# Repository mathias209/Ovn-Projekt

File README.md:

# Repo til vores ovnprojekt
beskrivelse go here

rapporter ligger i onedrive
rapport i word er her:
[Rapport](https://dtudk-my.sharepoint.com/:w:/r/personal/s256053_dtu_dk/Documents/Desktop/Projects/Ovn%20project.docx?d=wf24f0aff373c4a23b3fe023b4cf325e0&csf=1&web=1&e=GDiYzS)

[link til gruppe arbejde i Stens timer](https://github.com/mathias209/Elektroteknik-gruppearbejde)

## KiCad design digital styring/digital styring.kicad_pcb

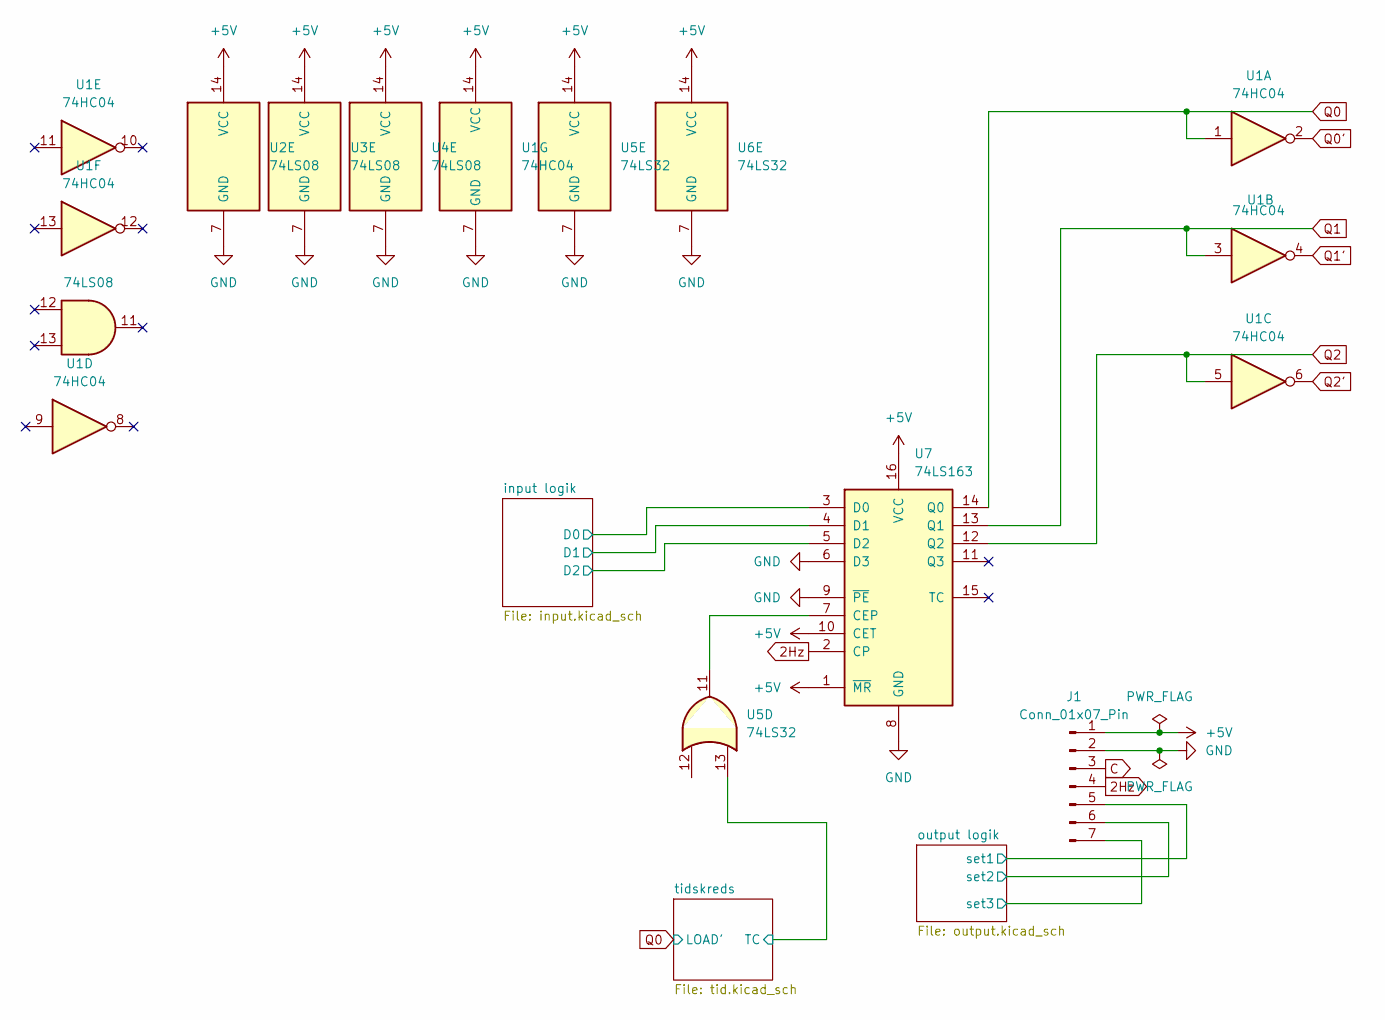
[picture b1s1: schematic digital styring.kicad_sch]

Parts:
J1: Conn_01x07_Pin; PinSocket_1x07_P2.54mm_Vertical
U1: 74HC04; DIP-14_W7.62mm_LongPads
U2, U3, U4: 74LS08; DIP-14_W7.62mm_LongPads
U5, U6: 74LS32; DIP-14_W7.62mm_LongPads
U7: 74LS163; DIP-16_W7.62mm_LongPads

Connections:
2Hz: J1.4, U7.2 (CP); also elsewhere on the board
+5V: J1.1, U1.14 (VCC), U2.14 (VCC), U3.14 (VCC), U4.14 (VCC), U5.14 (VCC), U6.14 (VCC), U7.1 (~MR), U7.10 (CET), U7.16 (VCC); also elsewhere on the board
/input logik/D0: U7.3 (D0); also elsewhere on the board
/input logik/D1: U7.4 (D1); also elsewhere on the board
/input logik/D2: U7.5 (D2); also elsewhere on the board
/output logik/set2: J1.6; also elsewhere on the board
/tidskreds/TC: U5.13; also elsewhere on the board
C: J1.3; also elsewhere on the board
GND: J1.2, U1.7 (GND), U2.7 (GND), U3.7 (GND), U4.7 (GND), U5.7 (GND), U6.7 (GND), U7.6 (D3), U7.8 (GND), U7.9 (~PE); also elsewhere on the board
unnamed: U5.11, U7.7 (CEP)
Q0: U1.1, U7.14 (Q0); also elsewhere on the board
Q0': U1.2, U5.12; also elsewhere on the board
Q1: U1.3, U7.13 (Q1); also elsewhere on the board
Q1': J1.5, U1.4
Q2: J1.7, U1.5, U7.12 (Q2); also elsewhere on the board
Q2': U1.6; also elsewhere on the board

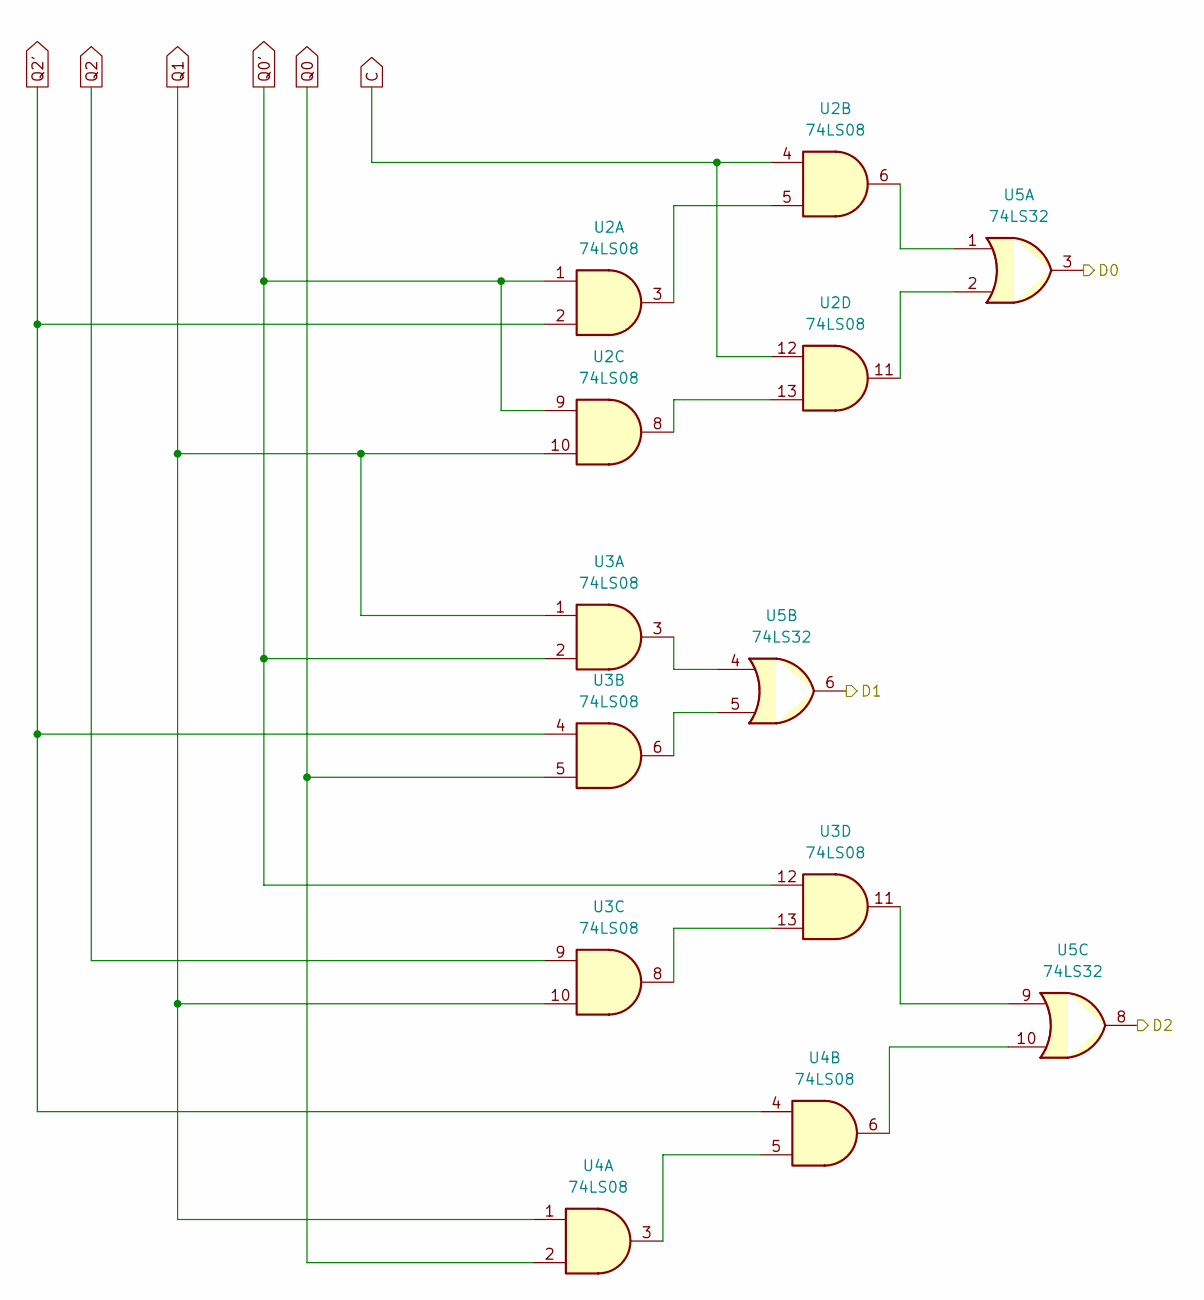
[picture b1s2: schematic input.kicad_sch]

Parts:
U2, U3, U4: 74LS08; DIP-14_W7.62mm_LongPads
U5: 74LS32; DIP-14_W7.62mm_LongPads

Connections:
/input logik/D0: U5.3; also elsewhere on the board
/input logik/D1: U5.6; also elsewhere on the board
/input logik/D2: U5.8; also elsewhere on the board
C: U2.4, U2.12; also elsewhere on the board
unnamed: U2.3, U2.5
unnamed: U2.6, U5.1
unnamed: U2.11, U5.2
unnamed: U2.8, U2.13
unnamed: U3.3, U5.4
unnamed: U3.6, U5.5
unnamed: U3.11, U5.9
unnamed: U3.8, U3.13
unnamed: U4.3, U4.5
unnamed: U4.6, U5.10
Q0: U3.5, U4.2; also elsewhere on the board
Q0': U2.1, U2.9, U3.2, U3.12; also elsewhere on the board
Q1: U2.10, U3.1, U3.10, U4.1; also elsewhere on the board
Q2: U3.9; also elsewhere on the board
Q2': U2.2, U3.4, U4.4; also elsewhere on the board

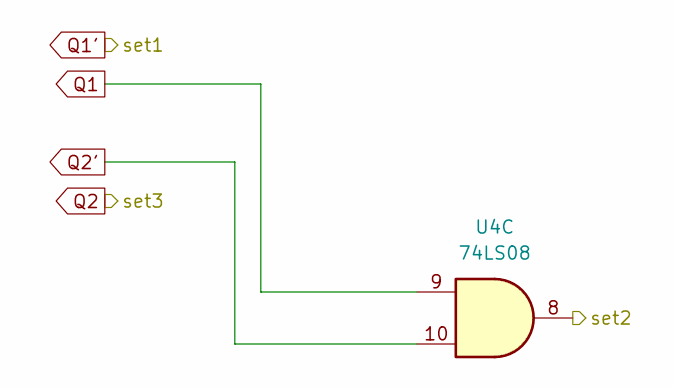
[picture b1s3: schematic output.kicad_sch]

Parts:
U4: 74LS08; DIP-14_W7.62mm_LongPads

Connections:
/output logik/set2: U4.8; also elsewhere on the board
Q1: U4.9; also elsewhere on the board
Q2': U4.10; also elsewhere on the board

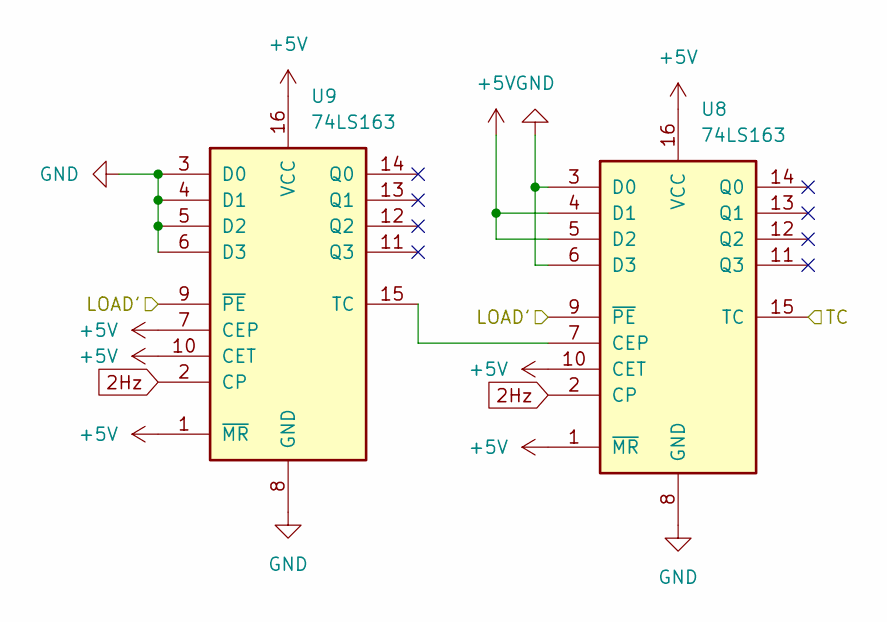
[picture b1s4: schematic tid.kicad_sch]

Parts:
U8, U9: 74LS163; DIP-16_W7.62mm_LongPads

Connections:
2Hz: U8.2 (CP), U9.2 (CP); also elsewhere on the board
+5V: U8.1 (~MR), U8.4 (D1), U8.5 (D2), U8.10 (CET), U8.16 (VCC), U9.1 (~MR), U9.7 (CEP), U9.10 (CET), U9.16 (VCC); also elsewhere on the board
/tidskreds/TC: U8.15 (TC); also elsewhere on the board
GND: U8.3 (D0), U8.6 (D3), U8.8 (GND), U9.3 (D0), U9.4 (D1), U9.5 (D2), U9.6 (D3), U9.8 (GND); also elsewhere on the board
unnamed: U8.7 (CEP), U9.15 (TC)
Q0: U8.9 (~PE), U9.9 (~PE); also elsewhere on the board

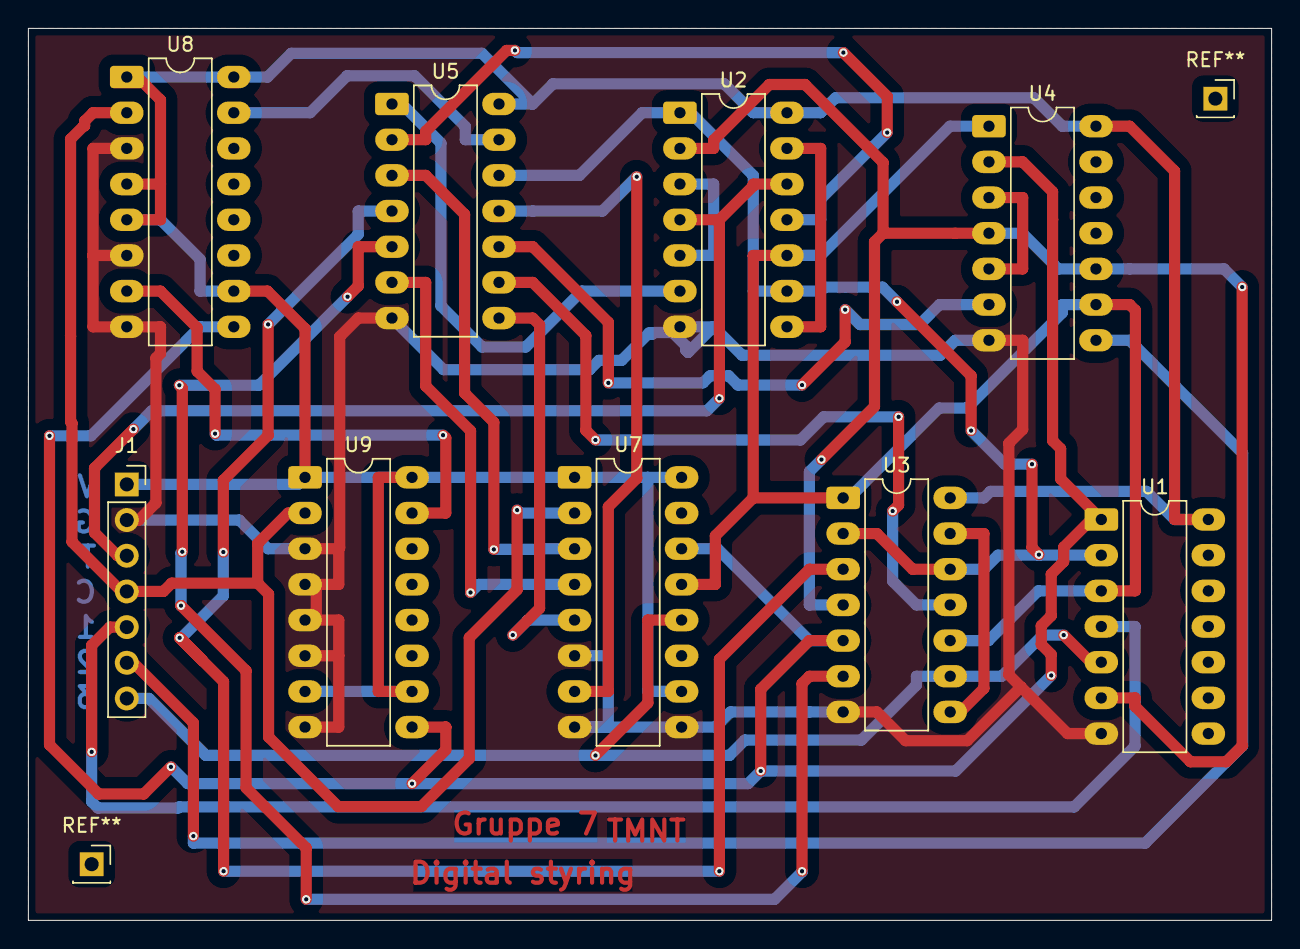
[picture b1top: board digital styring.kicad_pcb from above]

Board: 2 copper layers, 88.5 x 63.5 mm, 9 parts (0 on the bottom side), 27 nets.

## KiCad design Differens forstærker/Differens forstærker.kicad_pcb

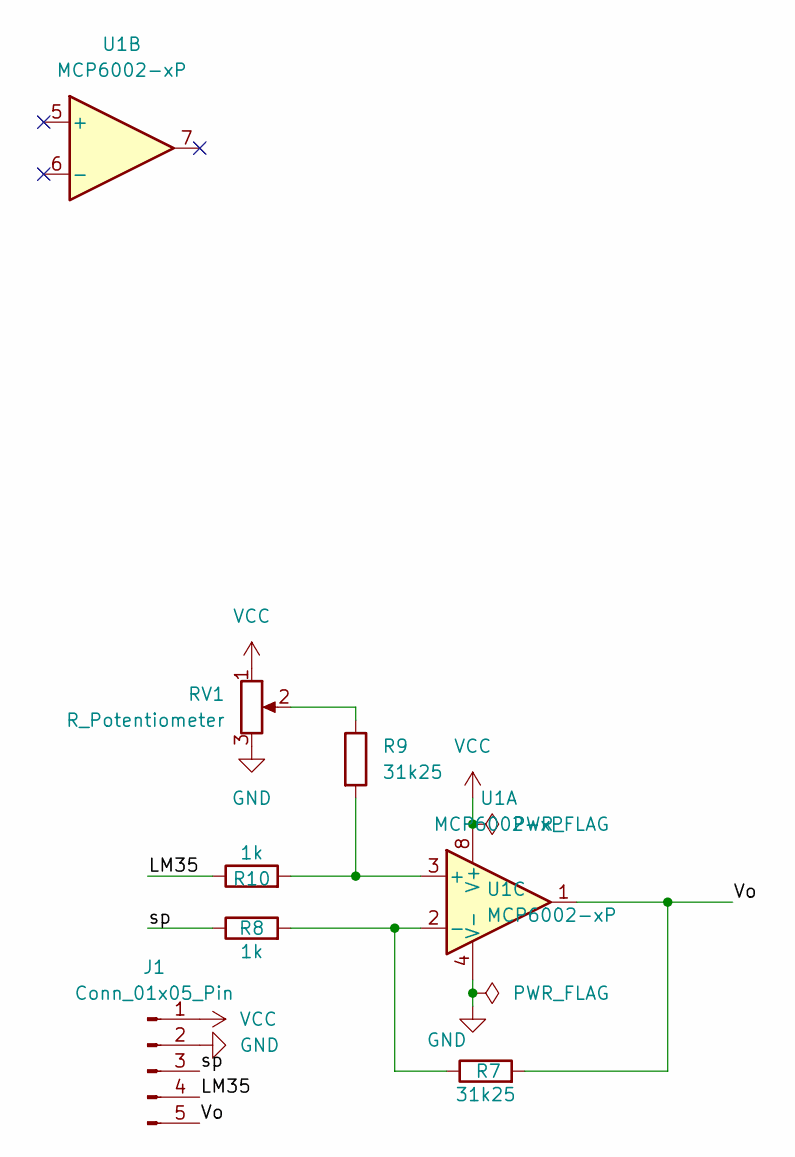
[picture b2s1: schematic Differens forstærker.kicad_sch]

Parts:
J1: Conn_01x05_Pin; PinSocket_1x05_P2.54mm_Vertical
R7, R9: 31k25; R_Axial_DIN0204_L3.6mm_D1.6mm_P7.62mm_Horizontal
R8, R10: 1k; R_Axial_DIN0204_L3.6mm_D1.6mm_P7.62mm_Horizontal
RV1: R_Potentiometer; Potentiometer_Bourns_3296W_Vertical
U1: MCP6002-xP; DIP-8_W7.62mm_LongPads

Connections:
/LM35: J1.4, R10.1
/Vo: J1.5, R7.2, U1.1
/sp: J1.3, R8.1
GND: J1.2, RV1.3, U1.4 (V-)
unnamed: R9.1, RV1.2
unnamed: R9.2, R10.2, U1.3 (+)
unnamed: R7.1, R8.2, U1.2 (-)
VCC: J1.1, RV1.1, U1.8 (V+)

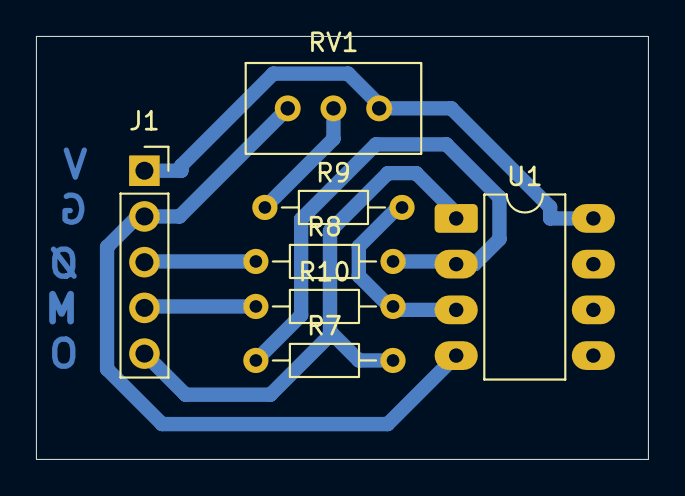
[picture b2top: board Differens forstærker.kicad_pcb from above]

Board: 2 copper layers, 34.0 x 23.5 mm, 7 parts (0 on the bottom side), 8 nets.

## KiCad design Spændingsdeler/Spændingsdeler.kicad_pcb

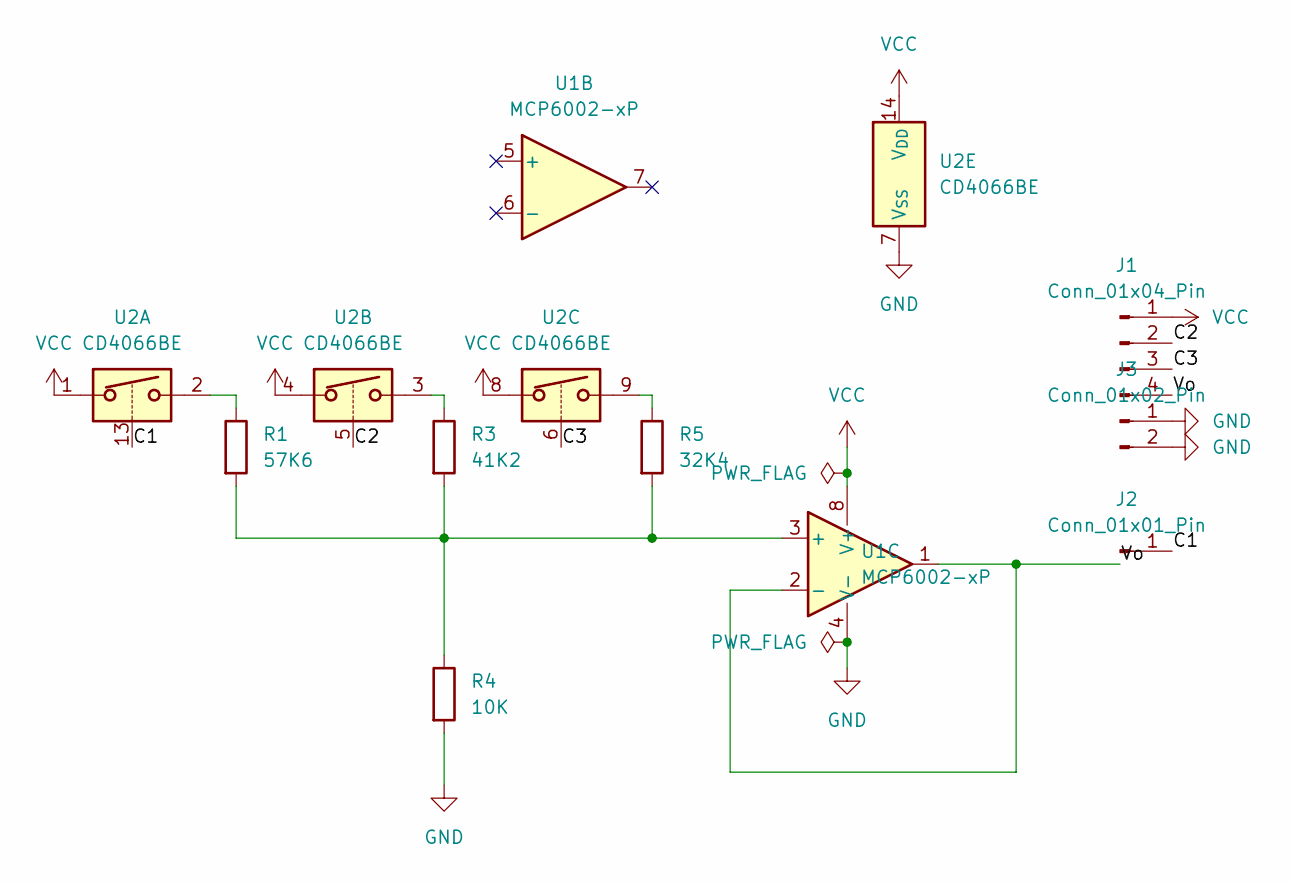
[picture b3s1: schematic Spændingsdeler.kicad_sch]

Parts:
J1: Conn_01x04_Pin; PinSocket_1x04_P2.54mm_Vertical
J2: Conn_01x01_Pin; PinSocket_1x01_P2.54mm_Vertical
J3: Conn_01x02_Pin; PinSocket_1x02_P2.54mm_Vertical
R1: 57K6; R_Axial_DIN0204_L3.6mm_D1.6mm_P7.62mm_Horizontal
R3: 41K2; R_Axial_DIN0204_L3.6mm_D1.6mm_P7.62mm_Horizontal
R4: 10K; R_Axial_DIN0204_L3.6mm_D1.6mm_P7.62mm_Horizontal
R5: 32K4; R_Axial_DIN0204_L3.6mm_D1.6mm_P7.62mm_Horizontal
U1: MCP6002-xP; DIP-8_W7.62mm_LongPads
U2: CD4066BE; DIP-14_W7.62mm_LongPads

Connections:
/C1: J2.1, U2.13
/C2: J1.2, U2.5
/C3: J1.3, U2.6
/Vo: J1.4, U1.1, U1.2 (-)
GND: J3.1, J3.2, R4.2, U1.4 (V-), U2.7 (V_{SS})
unnamed: R1.1, U2.2
unnamed: R3.1, U2.3
unnamed: R5.1, U2.9
unnamed: R1.2, R3.2, R4.1, R5.2, U1.3 (+)
VCC: J1.1, U1.8 (V+), U2.1, U2.4, U2.8, U2.14 (V_{DD})

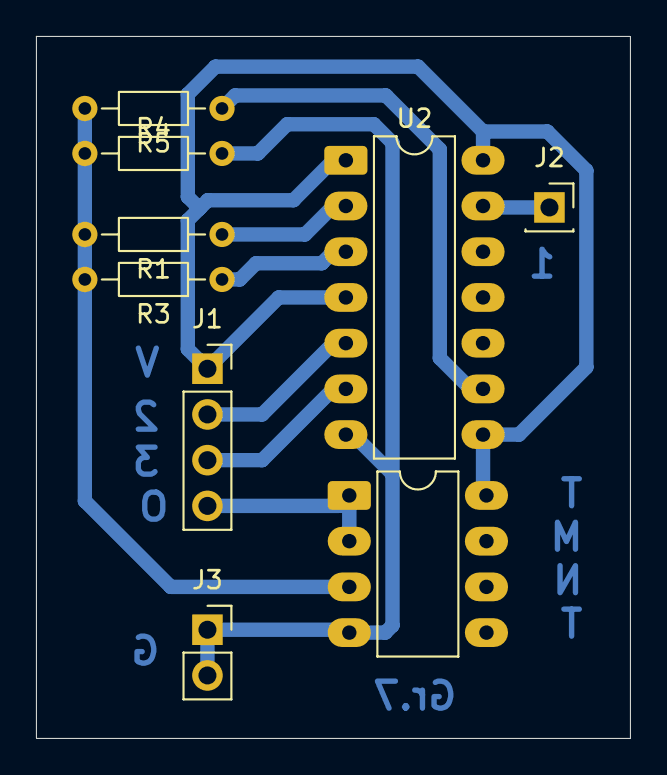
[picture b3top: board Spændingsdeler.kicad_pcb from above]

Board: 2 copper layers, 33.0 x 39.0 mm, 9 parts (0 on the bottom side), 10 nets.

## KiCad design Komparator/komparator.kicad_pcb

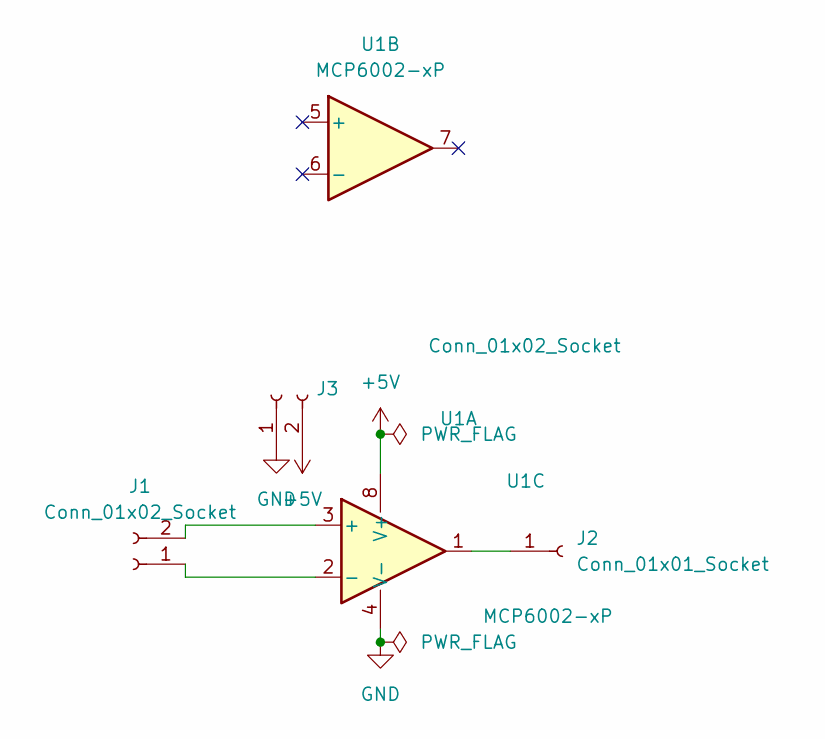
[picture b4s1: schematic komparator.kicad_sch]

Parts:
J1, J3: Conn_01x02_Socket; PinSocket_1x02_P2.54mm_Vertical
J2: Conn_01x01_Socket; PinSocket_1x01_P2.54mm_Vertical
U1: MCP6002-xP; DIP-8_W7.62mm_Socket

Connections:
+5V: J3.2, U1.8 (V+)
GND: J3.1, U1.4 (V-)
unnamed: J1.1, U1.2 (-)
unnamed: J1.2, U1.3 (+)
unnamed: J2.1, U1.1

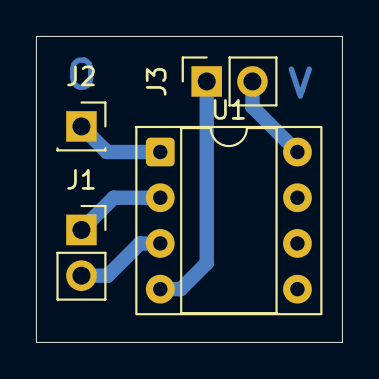
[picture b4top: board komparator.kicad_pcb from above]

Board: 2 copper layers, 17.0 x 17.0 mm, 4 parts (0 on the bottom side), 5 nets.

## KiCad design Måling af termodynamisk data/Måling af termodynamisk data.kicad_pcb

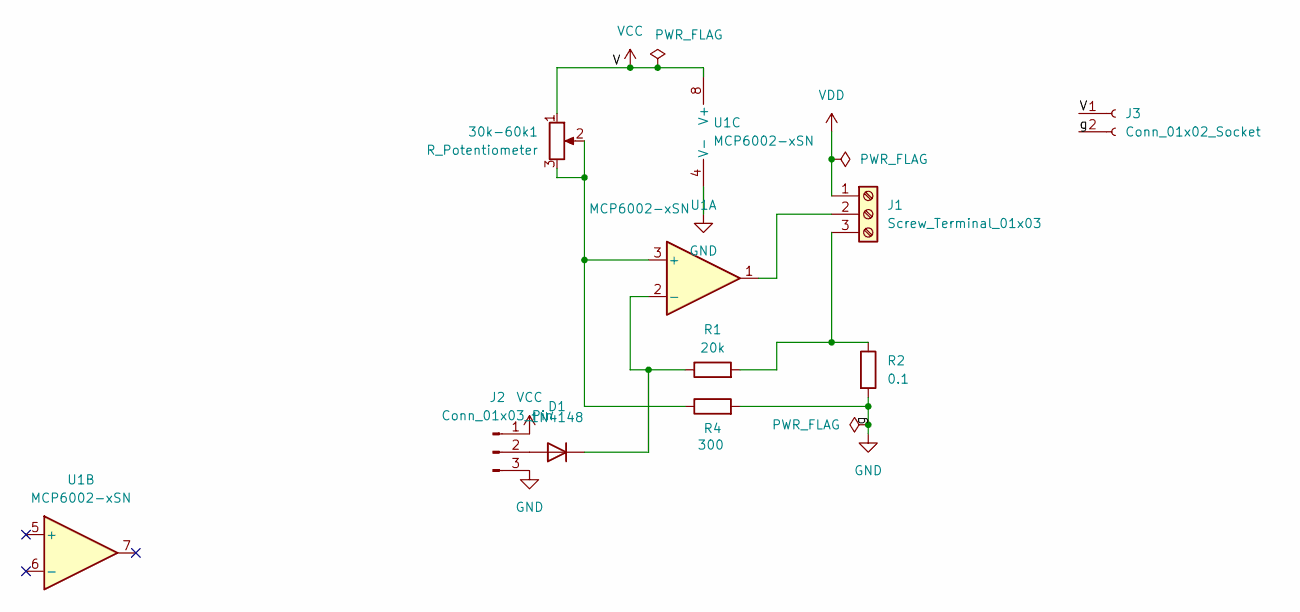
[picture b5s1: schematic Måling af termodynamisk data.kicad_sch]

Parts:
30k-60k1: R_Potentiometer; Potentiometer_ACP_CA9-V10_Vertical
D1: 1N4148; D_DO-35_SOD27_P7.62mm_Horizontal
J1: Screw_Terminal_01x03; TerminalBlock_bornier-3_P5.08mm
J2: Conn_01x03_Pin; PinHeader_1x03_P2.54mm_Vertical
J3: Conn_01x02_Socket; PinHeader_1x02_P2.54mm_Vertical
R1: 20k; R_Axial_DIN0204_L3.6mm_D1.6mm_P7.62mm_Horizontal
R2: 0.1; R_Axial_DIN0204_L3.6mm_D1.6mm_P7.62mm_Horizontal
R4: 300; R_Axial_DIN0204_L3.6mm_D1.6mm_P7.62mm_Horizontal
U1: MCP6002-xSN; DIP-8_W7.62mm_LongPads

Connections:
GND: J2.3, J3.2, R2.2, R4.2, U1.4 (V-)
unnamed: D1.2 (A), J2.2
unnamed: D1.1 (K), R1.1, U1.2 (-)
unnamed: J1.2, U1.1
unnamed: J1.3, R1.2, R2.1
unnamed: 30k-60k1.2, 30k-60k1.3, R4.1, U1.3 (+)
VCC: 30k-60k1.1, J2.1, J3.1, U1.8 (V+)
VDD: J1.1

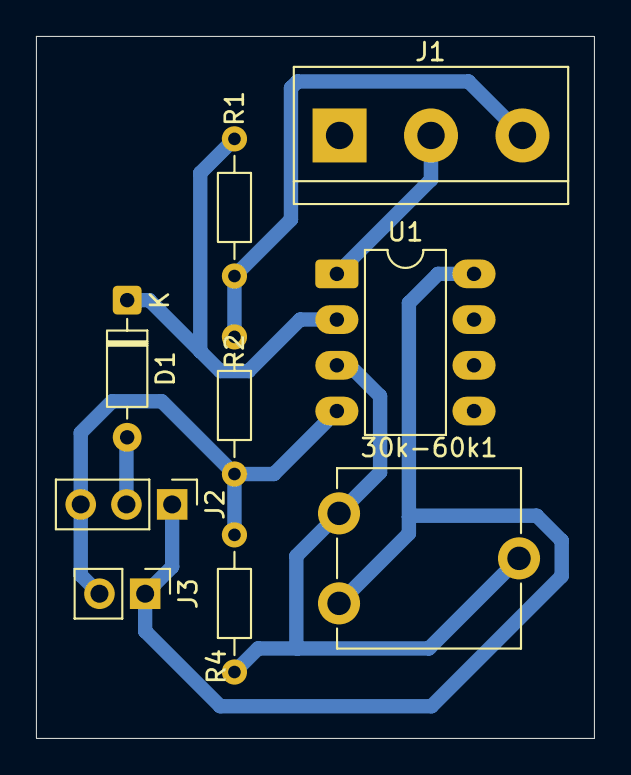
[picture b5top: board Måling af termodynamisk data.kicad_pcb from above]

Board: 2 copper layers, 31.0 x 39.0 mm, 9 parts (0 on the bottom side), 7 nets.

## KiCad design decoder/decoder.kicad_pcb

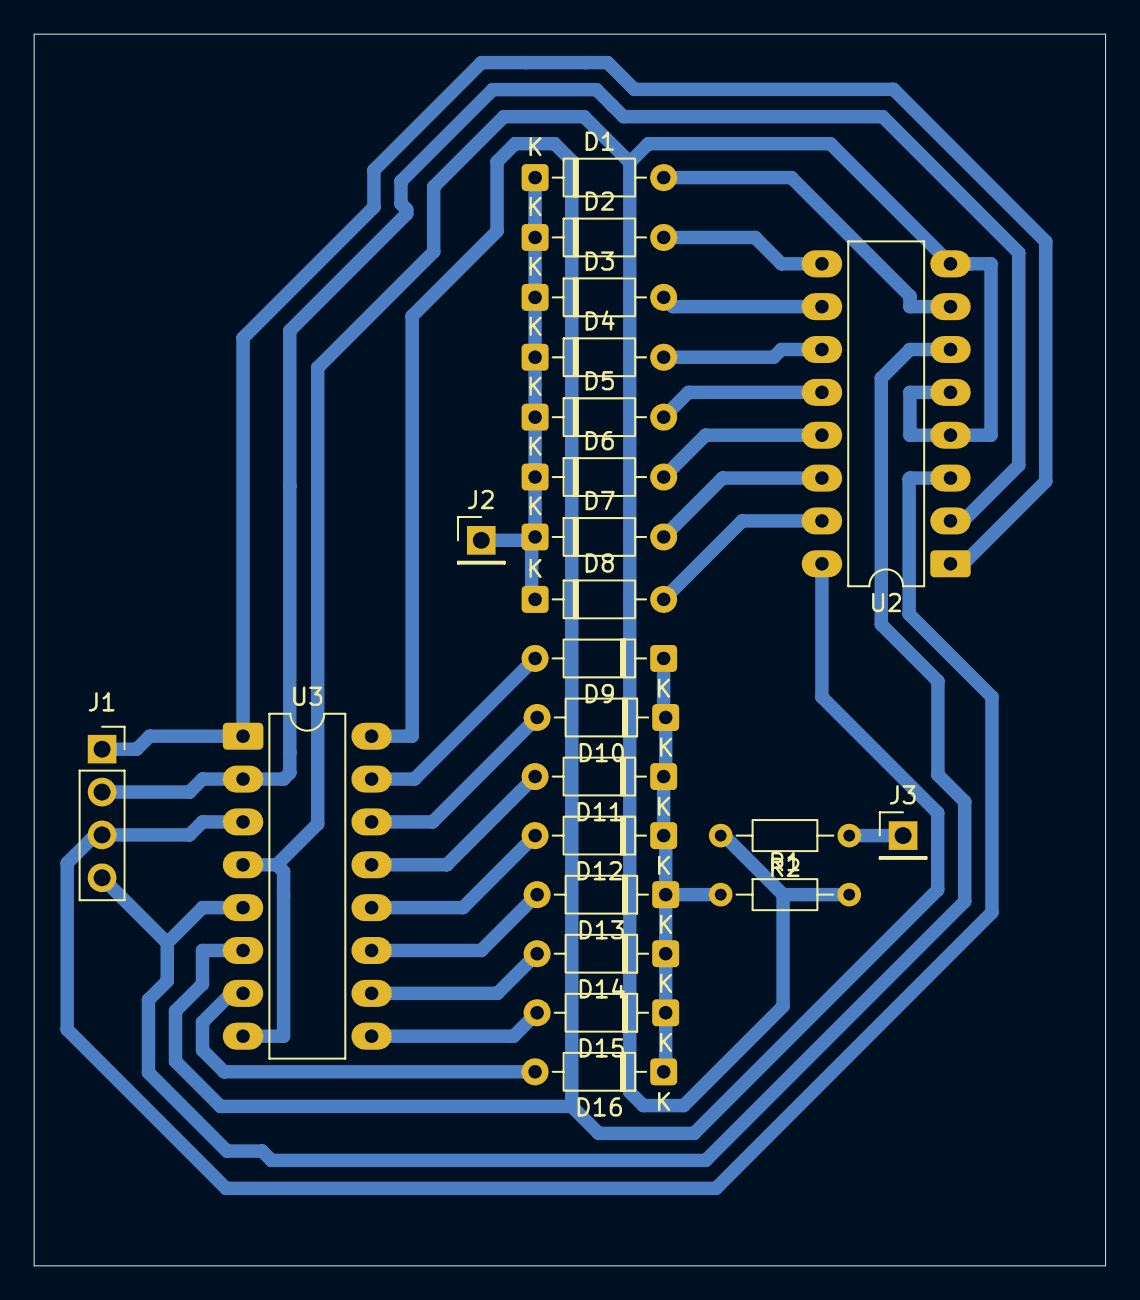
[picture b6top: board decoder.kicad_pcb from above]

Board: 2 copper layers, 63.5 x 73.0 mm, 23 parts (0 on the bottom side), 25 nets.

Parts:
D1, D2, D3, D4, D5, D6, D7, D8, D9, D10, D11, D12, D13, D14, D15, D16: 1N4148WT; D_DO-35_SOD27_P7.62mm_Horizontal
J1: Conn_01x04_Socket; PinSocket_1x04_P2.54mm_Vertical
J2, J3: Conn_01x01_Pin; PinHeader_1x01_P2.54mm_Vertical
R1, R2: R; R_Axial_DIN0204_L3.6mm_D1.6mm_P7.62mm_Horizontal
U2, U3: 74HC238; DIP-16_W7.62mm_LongPads

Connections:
GND: R1.2, R2.2, U2.4 (~E1), U2.5 (~E2), U2.8 (GND), U3.4 (~E1), U3.8 (GND)
unnamed: D1.2 (A), U2.7 (Y7)
unnamed: D1.1 (K), D2.1 (K), D3.1 (K), D4.1 (K), D5.1 (K), D6.1 (K), D7.1 (K), D8.1 (K), J2.1
unnamed: D2.2 (A), U2.9 (Y6)
unnamed: D3.2 (A), U2.10 (Y5)
unnamed: D4.2 (A), U2.11 (Y4)
unnamed: D5.2 (A), U2.12 (Y3)
unnamed: D6.2 (A), U2.13 (Y2)
unnamed: D7.2 (A), U2.14 (Y1)
unnamed: D8.2 (A), U2.15 (Y0)
unnamed: D9.2 (A), U3.15 (Y0)
unnamed: D10.2 (A), U3.14 (Y1)
unnamed: D9.1 (K), D10.1 (K), D11.1 (K), D12.1 (K), D13.1 (K), D14.1 (K), D15.1 (K), D16.1 (K), R1.1
unnamed: D11.2 (A), U3.13 (Y2)
unnamed: D12.2 (A), U3.12 (Y3)
unnamed: D13.2 (A), U3.11 (Y4)
unnamed: D14.2 (A), U3.10 (Y5)
unnamed: D15.2 (A), U3.9 (Y6)
unnamed: D16.2 (A), U3.7 (Y7)
unnamed: J1.1, U2.1 (A0), U3.1 (A0)
unnamed: J1.2, U2.2 (A1), U3.2 (A1)
unnamed: J1.3, U2.3 (A2), U3.3 (A2)
unnamed: J1.4, U2.6 (E3), U3.5 (~E2)
unnamed: J3.1, R2.1
VCC: U2.16 (VCC), U3.6 (E3), U3.16 (VCC)

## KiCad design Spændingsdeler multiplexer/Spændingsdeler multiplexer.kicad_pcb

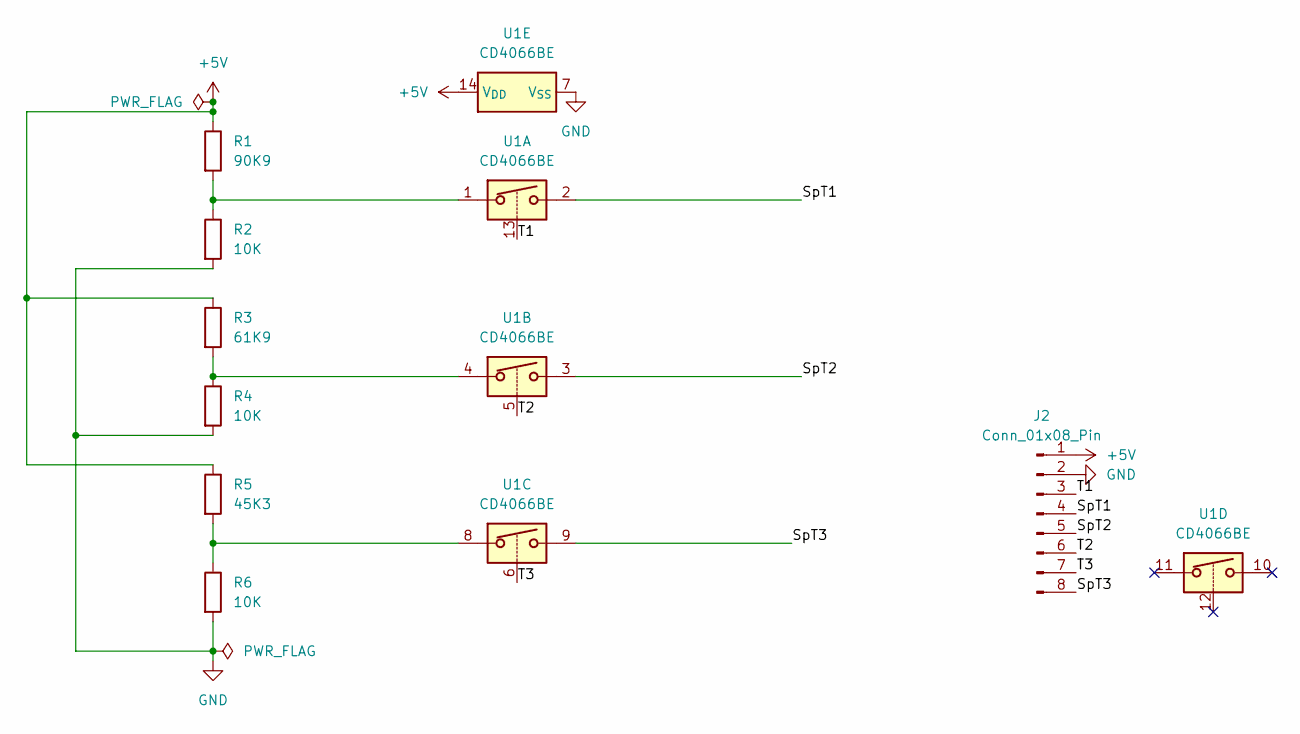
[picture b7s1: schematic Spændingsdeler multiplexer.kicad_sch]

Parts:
J2: Conn_01x08_Pin; PinSocket_1x08_P2.54mm_Vertical
R1: 90K9; R_Axial_DIN0204_L3.6mm_D1.6mm_P7.62mm_Horizontal
R2, R4, R6: 10K; R_Axial_DIN0204_L3.6mm_D1.6mm_P7.62mm_Horizontal
R3: 61K9; R_Axial_DIN0204_L3.6mm_D1.6mm_P7.62mm_Horizontal
R5: 45K3; R_Axial_DIN0204_L3.6mm_D1.6mm_P7.62mm_Horizontal
U1: CD4066BE; DIP-14_W7.62mm_LongPads

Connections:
+5V: J2.1, R1.1, R3.1, R5.1, U1.14 (V_{DD})
/SpT1: J2.4, U1.2
/SpT2: J2.5, U1.3
/SpT3: J2.8, U1.9
/T1: J2.3, U1.13
/T2: J2.6, U1.5
/T3: J2.7, U1.6
GND: J2.2, R2.2, R4.2, R6.2, U1.7 (V_{SS})
unnamed: R1.2, R2.1, U1.1
unnamed: R3.2, R4.1, U1.4
unnamed: R5.2, R6.1, U1.8

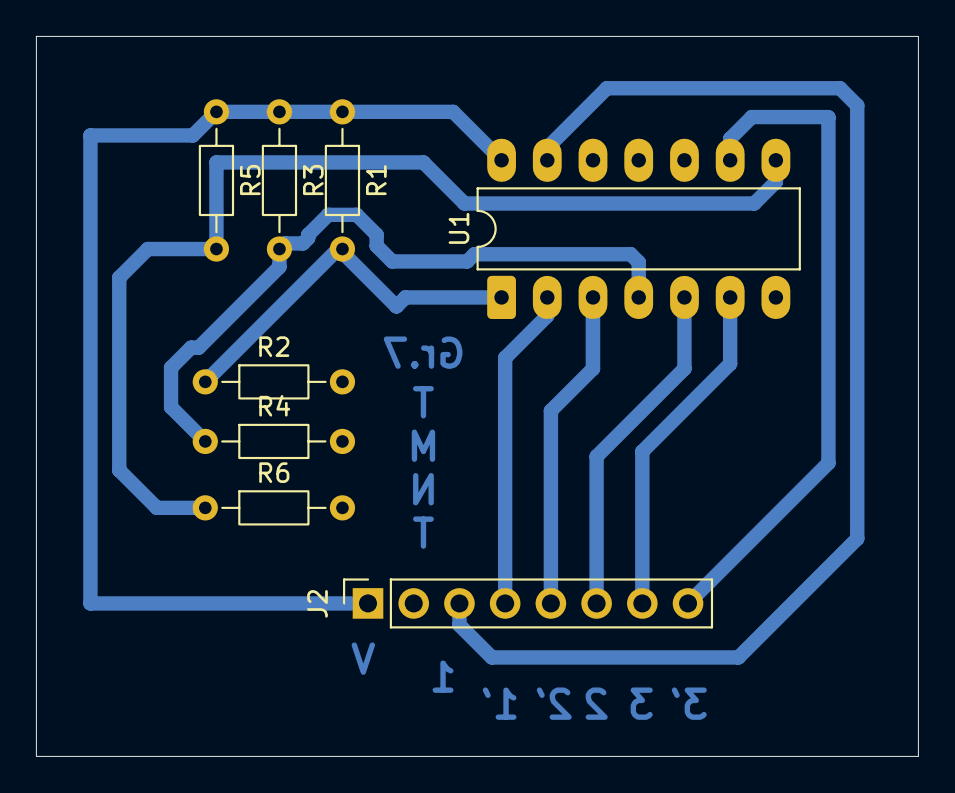
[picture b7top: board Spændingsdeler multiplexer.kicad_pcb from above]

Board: 2 copper layers, 49.0 x 40.0 mm, 8 parts (0 on the bottom side), 11 nets.

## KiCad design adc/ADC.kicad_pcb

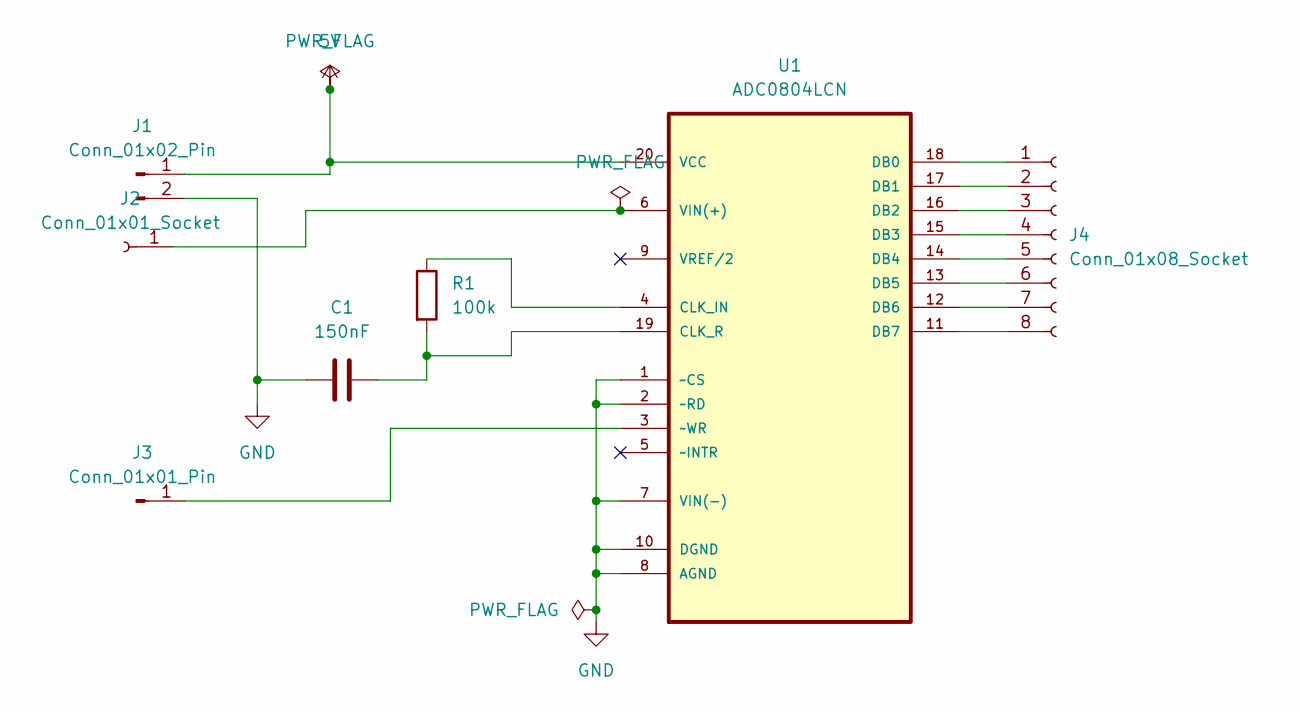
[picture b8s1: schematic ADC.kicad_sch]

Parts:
C1: 150nF; C_Axial_L3.8mm_D2.6mm_P7.50mm_Horizontal
J1: Conn_01x02_Pin; PinHeader_1x02_P2.54mm_Vertical
J2: Conn_01x01_Socket; PinSocket_1x01_P2.54mm_Vertical
J3: Conn_01x01_Pin; PinHeader_1x01_P2.54mm_Vertical
J4: Conn_01x08_Socket; PinSocket_1x08_P2.54mm_Vertical
R1: 100k; R_Axial_DIN0204_L3.6mm_D1.6mm_P7.62mm_Horizontal
U1: ADC0804LCN; DIP-20_W7.62mm_LongPads; MPN ADC0804LCN

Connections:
5V: J1.1, U1.20 (VCC)
GND: C1.1, J1.2, U1.1 (~CS), U1.2 (~RD), U1.7 (VIN(-)), U1.8 (AGND), U1.10 (DGND)
unnamed: J2.1, U1.6 (VIN(+))
unnamed: J3.1, U1.3 (~WR)
unnamed: J4.1, U1.18 (DB0)
unnamed: J4.2, U1.17 (DB1)
unnamed: J4.3, U1.16 (DB2)
unnamed: J4.4, U1.15 (DB3)
unnamed: J4.5, U1.14 (DB4)
unnamed: J4.6, U1.13 (DB5)
unnamed: J4.7, U1.12 (DB6)
unnamed: J4.8, U1.11 (DB7)
unnamed: R1.1, U1.4 (CLK_IN)
unnamed: C1.2, R1.2, U1.19 (CLK_R)

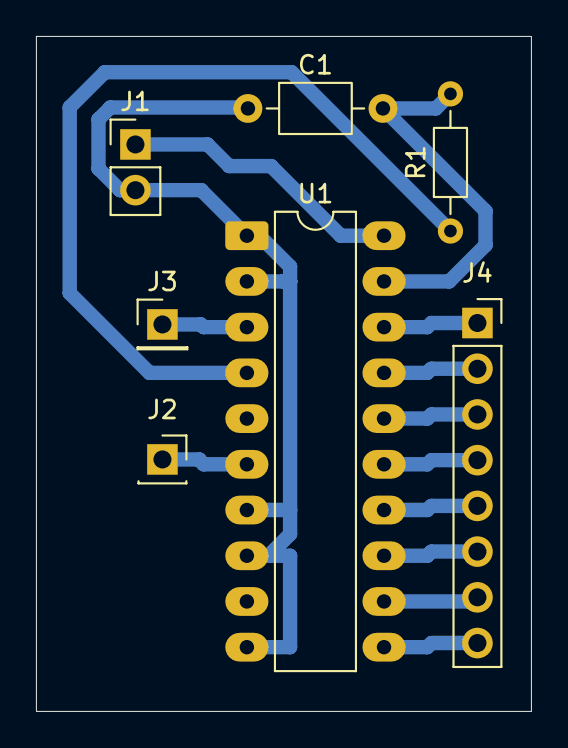
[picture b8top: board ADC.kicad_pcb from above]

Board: 2 copper layers, 27.5 x 37.5 mm, 7 parts (0 on the bottom side), 14 nets.

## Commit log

2025-09-12 tilføj opgave 1 og 2 fra lektion 1
2025-09-19 maple til ovn projekt og schematic
2025-09-19 schematic og pcb er færdig nr 1
2025-09-19 datablade
2025-09-19 første dxf fil til print af oscillator
2025-09-25 link til gruppearbejde
2025-09-26 ryttet op og tilføjet excel document til termodynamisk arametre
2025-09-26 maple pdf
2025-09-26 tester ting
2025-09-26 tester ting 2
2025-09-26 termodynamik schematic og pcb
2025-09-26 ting og sager
2025-10-01 digital oscillator færdig
2025-10-01 rapport pdf
2025-10-03 start af adc og decoder
2025-10-03 start af adc og decoder (fix)
2025-10-03 datablade til adc og decoder
2025-10-03 decoder færdig
2025-10-03 adc færdig
2025-10-03 lidt forskelligt
2025-10-22 måling af termodynamisk måling forhåbentlig færdig for tredje gang
2025-10-24 tilføjet differensforstærker kicad
2025-10-29 komparatormappe
2025-10-29 komparator upd.
2025-10-29 differens forstærker- de sidste udregninger og pcb
2025-10-31 komp mappestruktur
2025-10-31 spændingsdeler pcb med DXF
2025-10-31 tingog sager
2025-10-31 spændingsdeler små ting
2025-10-31 differens forstærker små fix
2025-10-31 bom til komerator
2025-11-03 DXF til differens forstærker og komperator
2025-11-07 test2
2025-11-07 booty
2025-11-07 ting
2025-11-09 termo ting
2025-11-09 start af hele ovnstyringen på et pcb
2025-11-12 spændingsfølger i spændingsdeleren
2025-11-14 tilstandsmaskine er noget tis
2025-11-14 tilstandsmaskine er noget tis #2
2025-11-21 digital styring pcb færdig(?)
2025-11-27 tis 2
2025-11-27 opdatering?
2025-11-27 tis 3
2025-11-27 finpudsning decoder
2025-11-27 deco done
2025-11-27 digital styring FÆRDIG
2025-11-28 måling tinf
2025-11-28 datahåndtering ting
2025-12-02 python datahåndtering meget bedre
2025-12-02 python datahåndtering lille fix
2025-12-03 python datahåndtering flere y akser næsten done
2025-12-03 python datahåndtering er helt færdig
2025-12-05 Projekt er færdig!!!
2025-12-07 alt muligt
